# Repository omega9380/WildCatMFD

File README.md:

# WildCatMFD
 An attempt at an open-source equivalent to the Thrustmaster Cougar MFD.
 
 It's designed around a 7" Lebula touchscreen monitor (available on [Amazon](https://www.amazon.com/gp/product/B07VNX4ZWY/ref=ppx_yo_dt_b_search_asin_title?ie=UTF8&psc=1)) and the Teensy 3.6 board using the Teensyduino Joystick library. 
 
 I went with the Teensy 3.6 so all the keys are direct-connect so as to avoid needing to design a button matrix or use shift registers, mostly because I have no idea where to start with those :).  I may come up with a version 2 (or 3 or 4....) that uses a smaller MC.
 
 I'm new to KiCAD and electronics and figured this would be a way to learn.
 
 I want this to conform to the OSHW initiative.  The code will be under the GPL.
 
 Thanks!

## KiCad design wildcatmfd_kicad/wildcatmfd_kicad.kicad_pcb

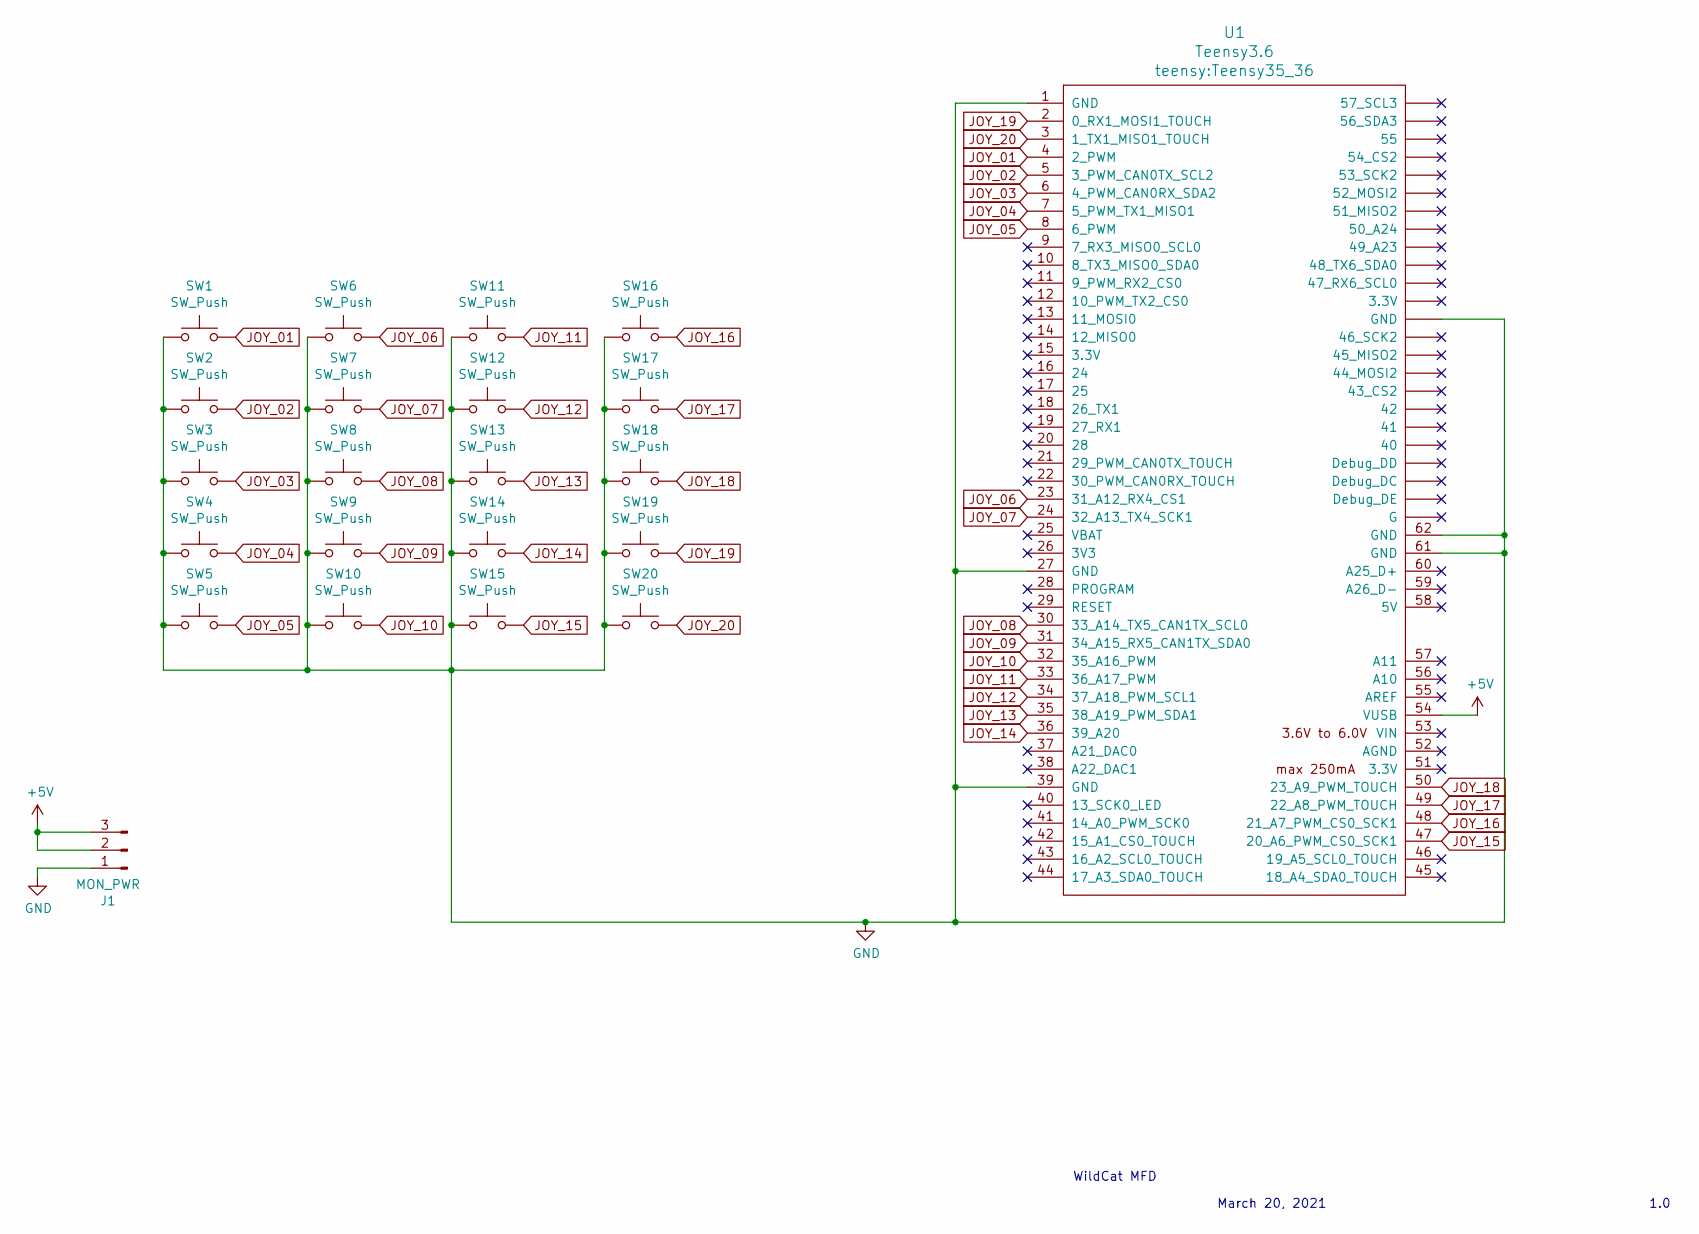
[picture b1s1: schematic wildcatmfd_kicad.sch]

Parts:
J1: MON_PWR; PinHeader_1x03_P2.54mm_Horizontal
SW1, SW2, SW3, SW4, SW5, SW6, SW7, SW8, SW9, SW10, SW11, SW12, SW13, SW14, SW15, SW16, SW17, SW18, SW19, SW20: SW_Push; SW_Cherry_MX_1.00u_PCB
U1: Teensy3.6; Teensy35_36

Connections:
+5V: J1.2, J1.3, U1.54 (VUSB)
GND: J1.1, SW1.1, SW2.1, SW3.1, SW4.1, SW5.1, SW6.1, SW7.1, SW8.1, SW9.1, SW10.1, SW11.1, SW12.1, SW13.1, SW14.1, SW15.1, SW16.1, SW17.1, SW18.1, SW19.1, SW20.1, U1.1 (GND), U1.27 (GND), U1.39 (GND), U1.61 (GND), U1.62 (GND), U1.~ (3.3V)
JOY_01: SW1.2, U1.4 (2_PWM)
JOY_02: SW2.2, U1.5 (3_PWM_CAN0TX_SCL2)
JOY_03: SW3.2, U1.6 (4_PWM_CAN0RX_SDA2)
JOY_04: SW4.2, U1.7 (5_PWM_TX1_MISO1)
JOY_05: SW5.2, U1.8 (6_PWM)
JOY_06: SW6.2, U1.23 (31_A12_RX4_CS1)
JOY_07: SW7.2, U1.24 (32_A13_TX4_SCK1)
JOY_08: SW8.2, U1.30 (33_A14_TX5_CAN1TX_SCL0)
JOY_09: SW9.2, U1.31 (34_A15_RX5_CAN1TX_SDA0)
JOY_10: SW10.2, U1.32 (35_A16_PWM)
JOY_11: SW11.2, U1.33 (36_A17_PWM)
JOY_12: SW12.2, U1.34 (37_A18_PWM_SCL1)
JOY_13: SW13.2, U1.35 (38_A19_PWM_SDA1)
JOY_14: SW14.2, U1.36 (39_A20)
JOY_15: SW15.2, U1.47 (20_A6_PWM_CS0_SCK1)
JOY_16: SW16.2, U1.48 (21_A7_PWM_CS0_SCK1)
JOY_17: SW17.2, U1.49 (22_A8_PWM_TOUCH)
JOY_18: SW18.2, U1.50 (23_A9_PWM_TOUCH)
JOY_19: SW19.2, U1.2 (0_RX1_MOSI1_TOUCH)
JOY_20: SW20.2, U1.3 (1_TX1_MISO1_TOUCH)

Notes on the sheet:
WildCat MFD
March 20, 2021
1.0

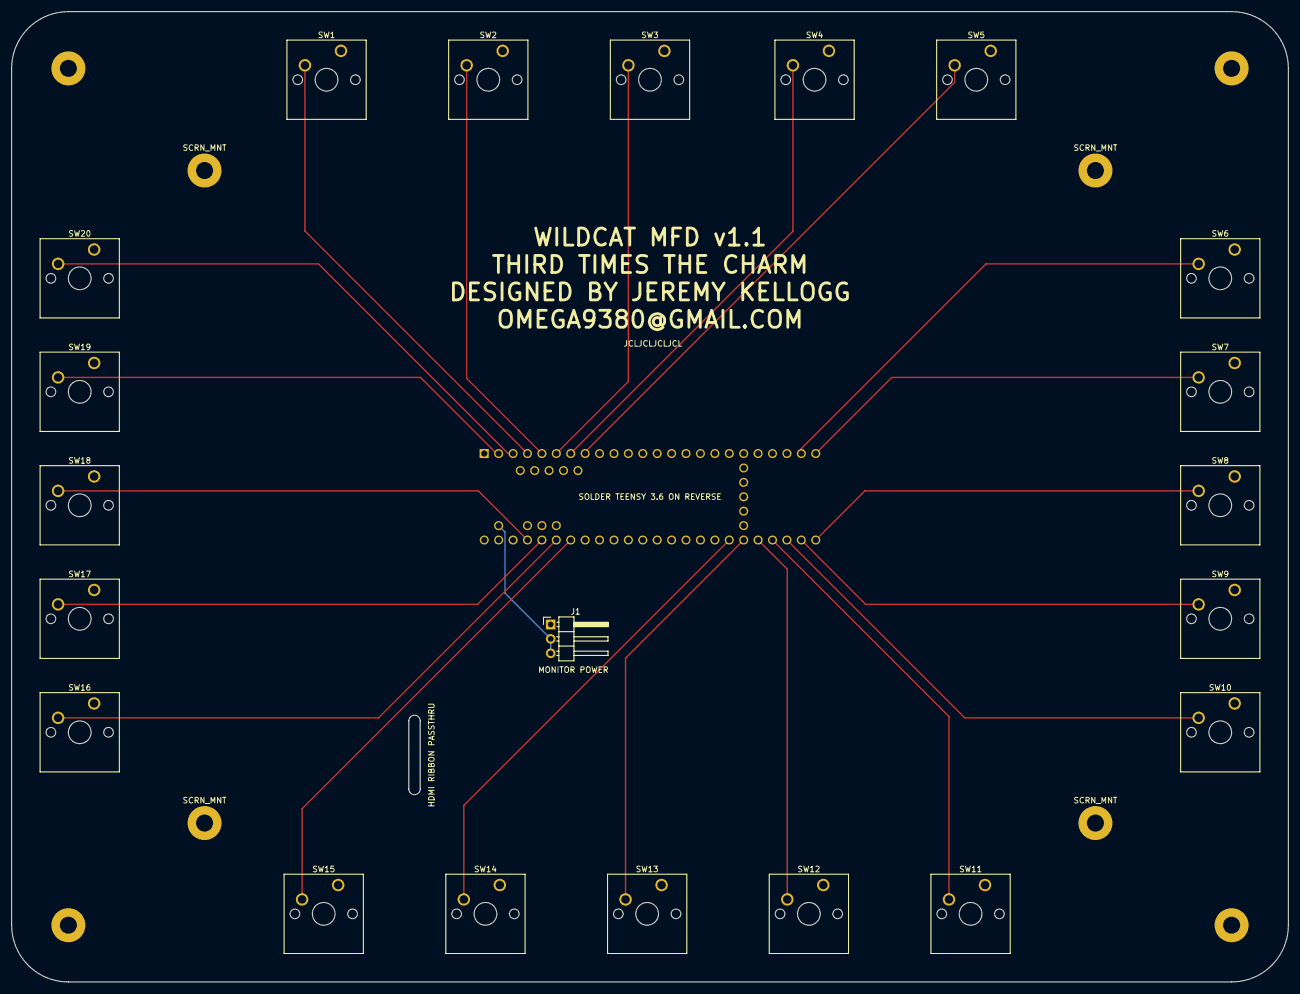
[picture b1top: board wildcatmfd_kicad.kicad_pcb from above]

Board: 2 copper layers, 225.0 x 171.0 mm, 26 parts (1 on the bottom side), 22 nets.

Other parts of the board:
SCRN_MNT: MountingHole_3mm_Pad
SCRN_MNT#2, SCRN_MNT#3, SCRN_MNT#4: MountingHole_3mm_Pad

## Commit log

2021-03-18 Started working on the board
2021-03-19 Update wildcatmfd_names.c
    Added MANUFACTURER_NAME
2021-03-19 Start again with KiCAD!
    Autodesk sucks. Starting anew while learning KiCAD!
2021-03-20 Playing with KiCAD
2021-03-20 Started Design
2021-03-21 Schematic done
    Need to design the board layout now
2021-03-21 Moved JOY_12 off of Pin 13
    Pin 13 is the LED on the Teensy, not recommended to be used as an input
2021-03-21 Update joystick.ino
    Updated code to exclude Pin 13
2021-03-26 Create WCMFD_BOARD.dxf
    Begin design of board outline for import into KiCAD
2021-03-26 Created QCAD file for board
    Created QCAD file for board outline
    Created measurment template of Lebula 7" screen to help with board layout
2021-03-27 More PCB work
2021-03-29 Version 1.0 Complete
    Will order PCBs!
2021-04-02 Added mounting holes
2021-04-02 Generate new Gerbers for PCBWay
2021-04-13 PCB 2.0
    First attempt - 20mm off on screen mount (doh!) - Redesigning PCB to include pass-thru hole for HDMI ribbon cable and adding 3 pin header for +5v for screen power
2021-04-14 More PCB work
    Finished component positioning
    Created board outline
    Placed holes for board mounts and screen mounts
    SEPTENVIGINTUPLE CHECKED SCREEN MOUNT MEASUREMENTS!
2021-04-14 Round 2
    Finished new design.
    Uploaded to JCLPCB for order.
2021-04-15 Update fp-info-cache
2021-04-29 Fixed again
    Adjusted location of HDMI cable pass-thru slot
    Remembered to turn the damned flood fill for the ground plane back on!
2021-05-08 Update joystick.ino
    Updated Teensy code
2021-05-26 Added dimension files from Lebula
    added informational files from Lebula with dimensions for the screen
2021-05-26 misc
